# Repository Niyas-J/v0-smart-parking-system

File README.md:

# v0-smart-parking-system

This is a [Next.js](https://nextjs.org) project bootstrapped with [v0](https://v0.app).

## Built with v0

This repository is linked to a [v0](https://v0.app) project. You can continue developing by visiting the link below -- start new chats to make changes, and v0 will push commits directly to this repo. Every merge to `main` will automatically deploy.

[Continue working on v0 →](https://v0.app/chat/projects/prj_UHsTBpqtMadH5lwPa28E3Ke8UXaq)

## Getting Started

First, run the development server:

```bash
npm run dev
# or
yarn dev
# or
pnpm dev
```

Open [http://localhost:3000](http://localhost:3000) with your browser to see the result.

You can start editing the page by modifying `app/page.tsx`. The page auto-updates as you edit the file.

## Learn More

To learn more, take a look at the following resources:

- [Next.js Documentation](https://nextjs.org/docs) - learn about Next.js features and API.
- [Learn Next.js](https://nextjs.org/learn) - an interactive Next.js tutorial.
- [v0 Documentation](https://v0.app/docs) - learn about v0 and how to use it.

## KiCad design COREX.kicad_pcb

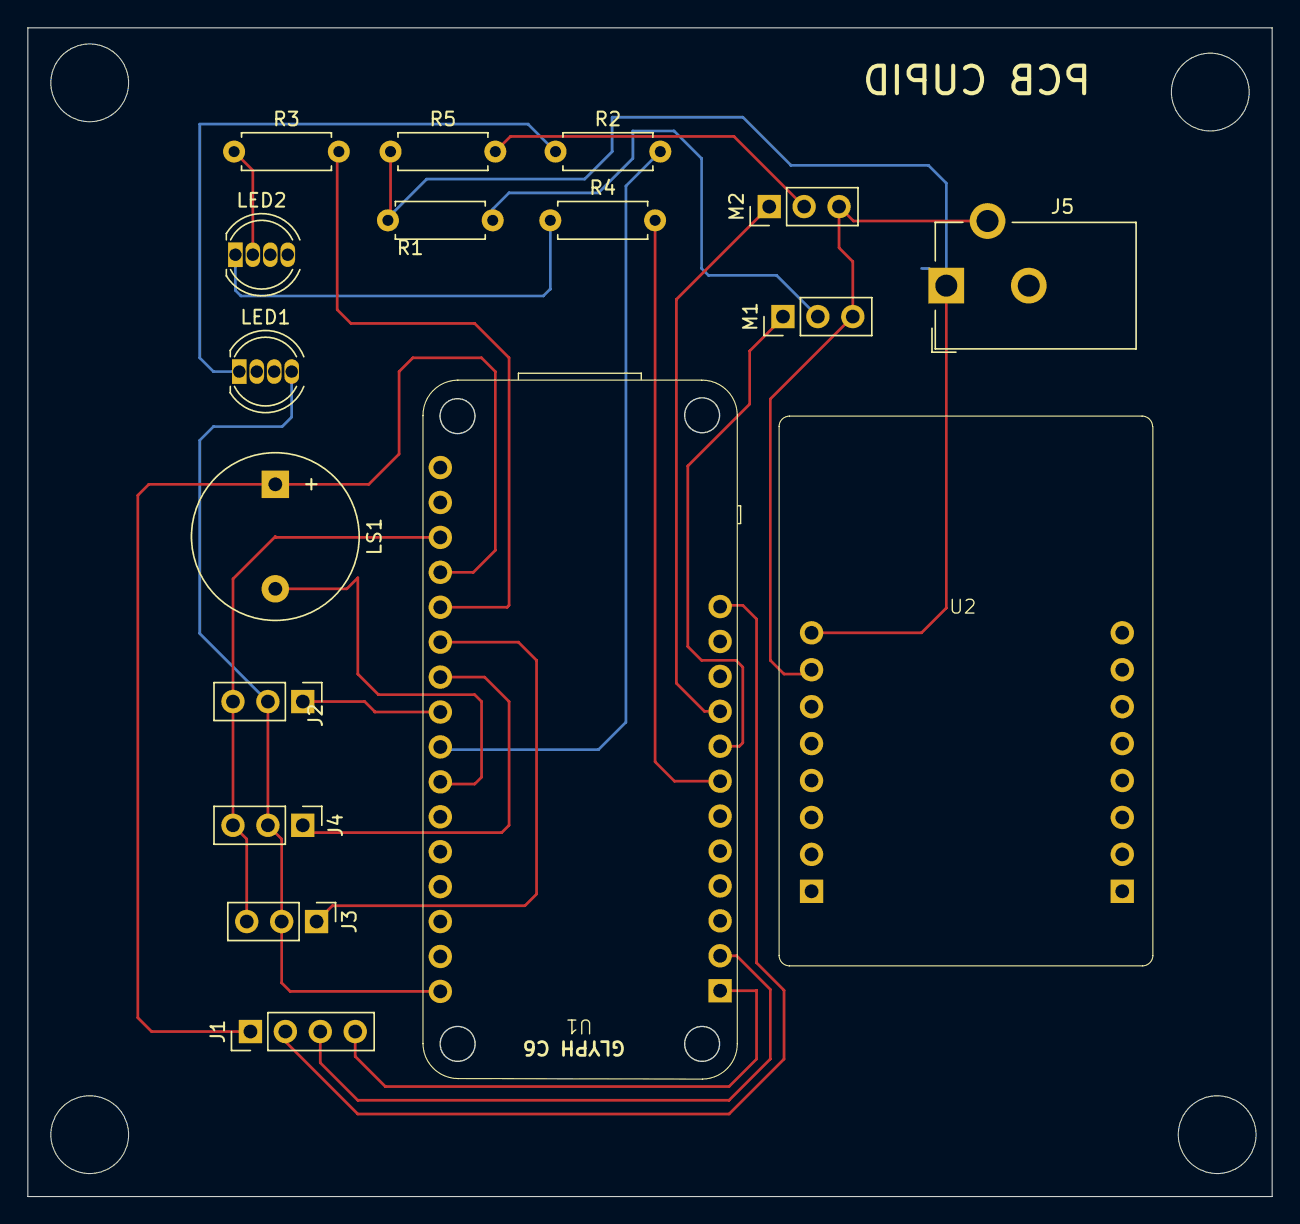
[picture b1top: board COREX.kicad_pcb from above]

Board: 2 copper layers, 90.4 x 85.0 mm, 17 parts (0 on the bottom side), 22 nets.

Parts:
J1: Conn_01x04_Pin; PinHeader_1x04_P2.54mm_Vertical
J2, J3, J4: Conn_01x03_Socket; PinHeader_1x03_P2.54mm_Vertical
J5: Barrel_Jack_Switch_Pin3Ring; BarrelJack_CUI_PJ-102AH_Horizontal
LED1, LED2: LED_D5.0mm-4_RGB
LS1: buzzer; Buzzer_12x9.5RM7.6
M1, M2: Motor_Servo; PinHeader_1x03_P2.54mm_Vertical
R1, R2, R3, R4, R5: R; R_Axial_DIN0207_L6.3mm_D2.5mm_P7.62mm_Horizontal
U1: glyph-c6
U2: esp32_cam

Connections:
unnamed: J1.1, LS1.1, U1.16 (GND)
unnamed: J1.2, U1.12 (BAT)
unnamed: J1.3, U1.2 (SDA)
unnamed: J1.4, U1.1 (SCL)
unnamed: J2.1, U1.20 (D18)
unnamed: J2.2, J3.2, J4.2, LED1.4 (GND), LED2.4 (GND), U1.28 (GND)
unnamed: J2.3, J3.3, J4.3, U1.15 (3V3)
unnamed: J3.1, U1.18 (D14)
unnamed: J4.1, U1.19 (D15)
unnamed: LED1.1 (R), R2.1
unnamed: LED2.2 (G), R3.1
unnamed: LED2.1 (R), R4.1
unnamed: M1.2 (+), R1.1
unnamed: J5.3, M1.3 (-), M2.3 (-), U2.3 (GND)
unnamed: M1.1 (PWM), U1.8 (D7)
unnamed: M2.2 (+), R5.2
unnamed: M2.1 (PWM), U1.9 (D8)
unnamed: R4.2, U1.7 (D6)
unnamed: R3.2, U1.17 (D9)
unnamed: R2.2, U1.21 (D19)
unnamed: LS1.2, U1.22 (D20)
unnamed: J5.1, R1.2, R5.1, U2.2 (5V)

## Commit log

2026-04-11 Initial commit from v0
2026-04-11 fix: add Node.js script for Neon migrations\n\nUse DATABASE_URL for proper Neon connection migrations.
2026-04-11 rename: convert run-migrations.mjs to run-migrations.js
2026-04-11 refactor: fix slot grid color syntax with Tailwind\n\nUpdate slot grid colors to use Tailwind classes instead of CSS variables.
2026-04-11 feat: make admin and user dashboard elements clickable\n\nAdd navigation to related pages and fix chart colors with Tailwind classes.
2026-04-11 Add README.md
2026-04-11 feat: enhance UI with glassmorphism and new pages
    Add Team, FAQ, and Enquiry pages; update landing with sponsors and navigation; enable guest dashboard access; apply glassmorphism design
2026-04-12 feat: premium 3D parking UI, analytics charts, zones, and admin live hub
    - Add Three.js/R3F interactive parking deck with glow states and car meshes
    - Glassmorphism layout, ambient gradients, framer-motion booking steps
    - Real-data Recharts on dashboard; analytics API and extended admin stats
    - Bike/Car/SUV zones, slot enrichment, optional SQL migration for 60+ bays
    - Admin alert stream with imagery, 12s polling, zone utilization charts
    Made-with: Cursor
2026-04-12 feat: direct booking without login page
    - Add /book with auto guest session (POST /api/auth/guest)
    - Redirect / and /login to /book; dashboard auth fallback to /book
    - Extract BookParkingContent; /dashboard/book redirects to /book
    - Nav and dashboard CTAs point to /book; register links to book flow
    Made-with: Cursor
2026-04-12 feat: 2D map UI, ESP32 hardware webhook, and enquiries system API
2026-04-12 add contact link to nav
2026-04-12 fix(vercel): remove pnpm-lock to resolve multi-lockfile error
2026-04-12 Fix authentication: Add password_hash column and update database schema
2026-04-12 Add deployment instructions for project owner
2026-04-12 chore: sync pnpm lockfile for vercel
2026-04-12 Add navigation sidebar to all dashboard and book pages
2026-04-12 Add navigation fix documentation
2026-04-12 Add ANPR system with client-side OCR
2026-04-12 Add ANPR system documentation
2026-04-12 Fix camera preview - add muted and play handlers
2026-04-12 feat: integrate Firebase Admin SDK for ESP32 image storage
2026-04-12 feat: add Firebase Client SDK
2026-04-12 Rewrite ANPR camera with better debugging and error handling
2026-04-12 Fix accessibility warning - add SheetTitle to navigation
2026-04-12 Add network dev script and phone testing guide
2026-04-12 Remove firebase dependency and update lockfile
2026-04-12 Force Vercel redeploy - fix pnpm lockfile issue
2026-04-12 Remove unused firebase files
2026-04-12 Add debug endpoint to test auth on production
2026-04-12 Fix bcrypt compatibility: regenerate hashes with bcryptjs, disable caching
